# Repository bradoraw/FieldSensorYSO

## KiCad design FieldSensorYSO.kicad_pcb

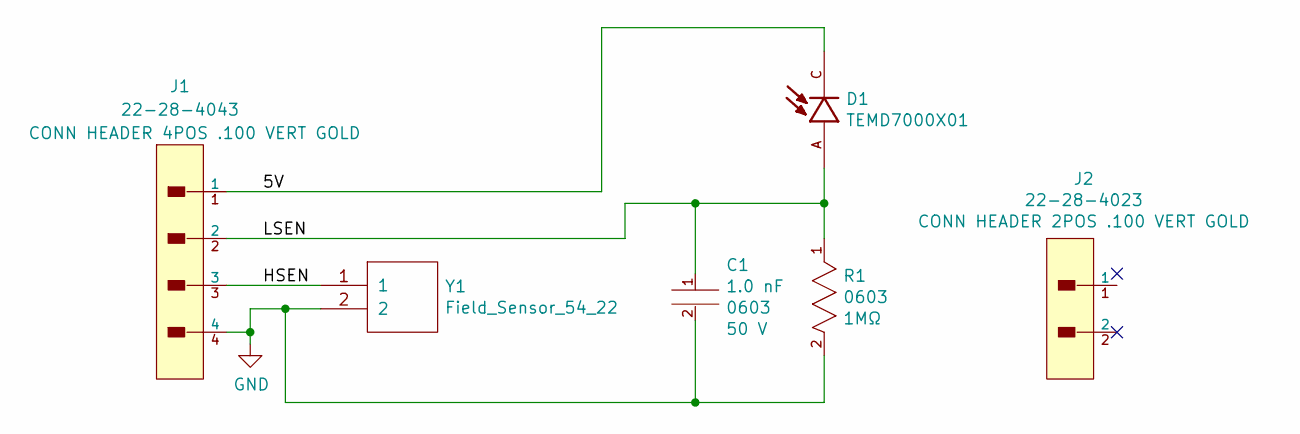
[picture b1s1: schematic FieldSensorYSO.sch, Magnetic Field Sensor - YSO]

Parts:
C1: CC0603KRX7R9BB102; YAGEO-CC0603-0-0-0; tolerance 0.1; voltage 50 V; mouser part number 603-CC603KRX7R9BB102; digikey description CAP CER 1000PF 50V X7R 0603
D1: TEMD7000X01; XDCR_TEMD7000X01
J1: 22-28-4043; Molex-SD-42375-001-0-0-0; Voltage Maximum 250V; voltage 250V; mouser part number 538-22-28-4043; digikey description CONN HEADER 4POS .100 VERT GOLD
J2: 22-28-4023; Molex-22-28-4023-0-0-0; current rating 4A; voltage rating 500V; mouser part number 538-22-28-4023; digikey description CONN HEADER 2POS .100 VERT GOLD
R1: RC0603FR-071ML; Yageo-RC0603-0-0-IPC_A; power rating 0.1W; tolerance 1%; mouser part number 311-1.00MHRTR-ND; digikey description RES SMD 1M OHM 1% 1/10W 0603
Y1: Field_Sensor_54_22

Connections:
/5V: D1.C, J1.1
/HSEN: J1.3, Y1.1
/LSEN: C1.1, D1.A, J1.2, R1.1
GND: C1.2, J1.4, R1.2, Y1.2

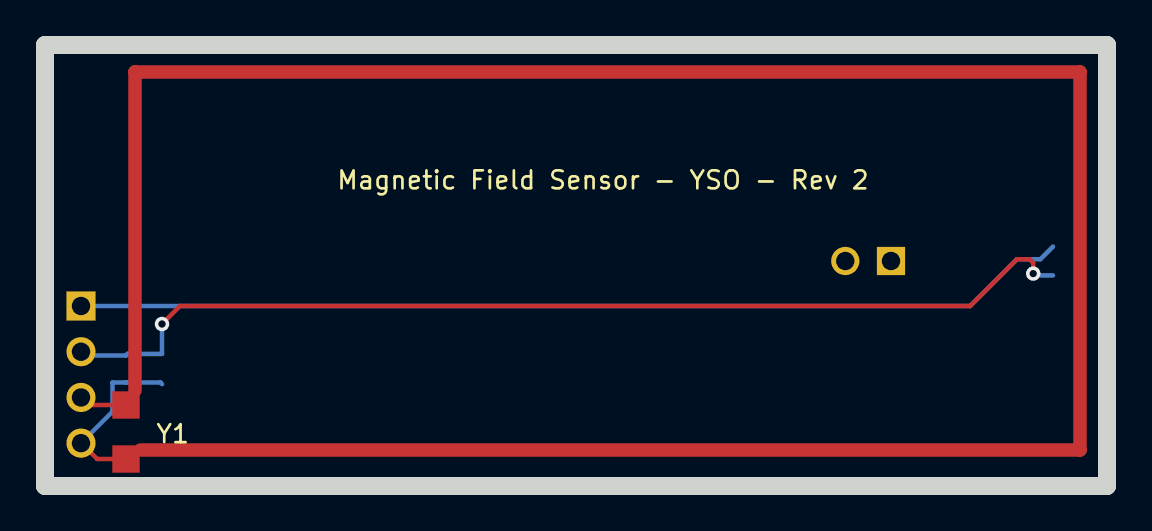
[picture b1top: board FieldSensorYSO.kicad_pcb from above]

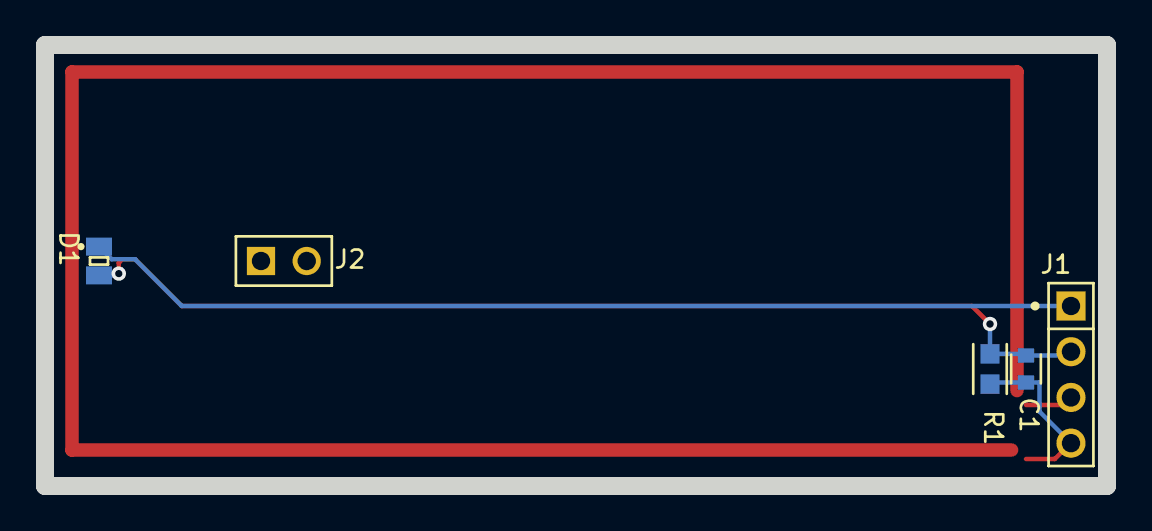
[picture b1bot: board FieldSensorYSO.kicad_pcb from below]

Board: 2 copper layers, 59.0 x 24.5 mm, 6 parts (5 on the bottom side), 4 nets.

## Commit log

2020-11-28 layout complete. manufacturing files.
2021-01-27 rev 2
